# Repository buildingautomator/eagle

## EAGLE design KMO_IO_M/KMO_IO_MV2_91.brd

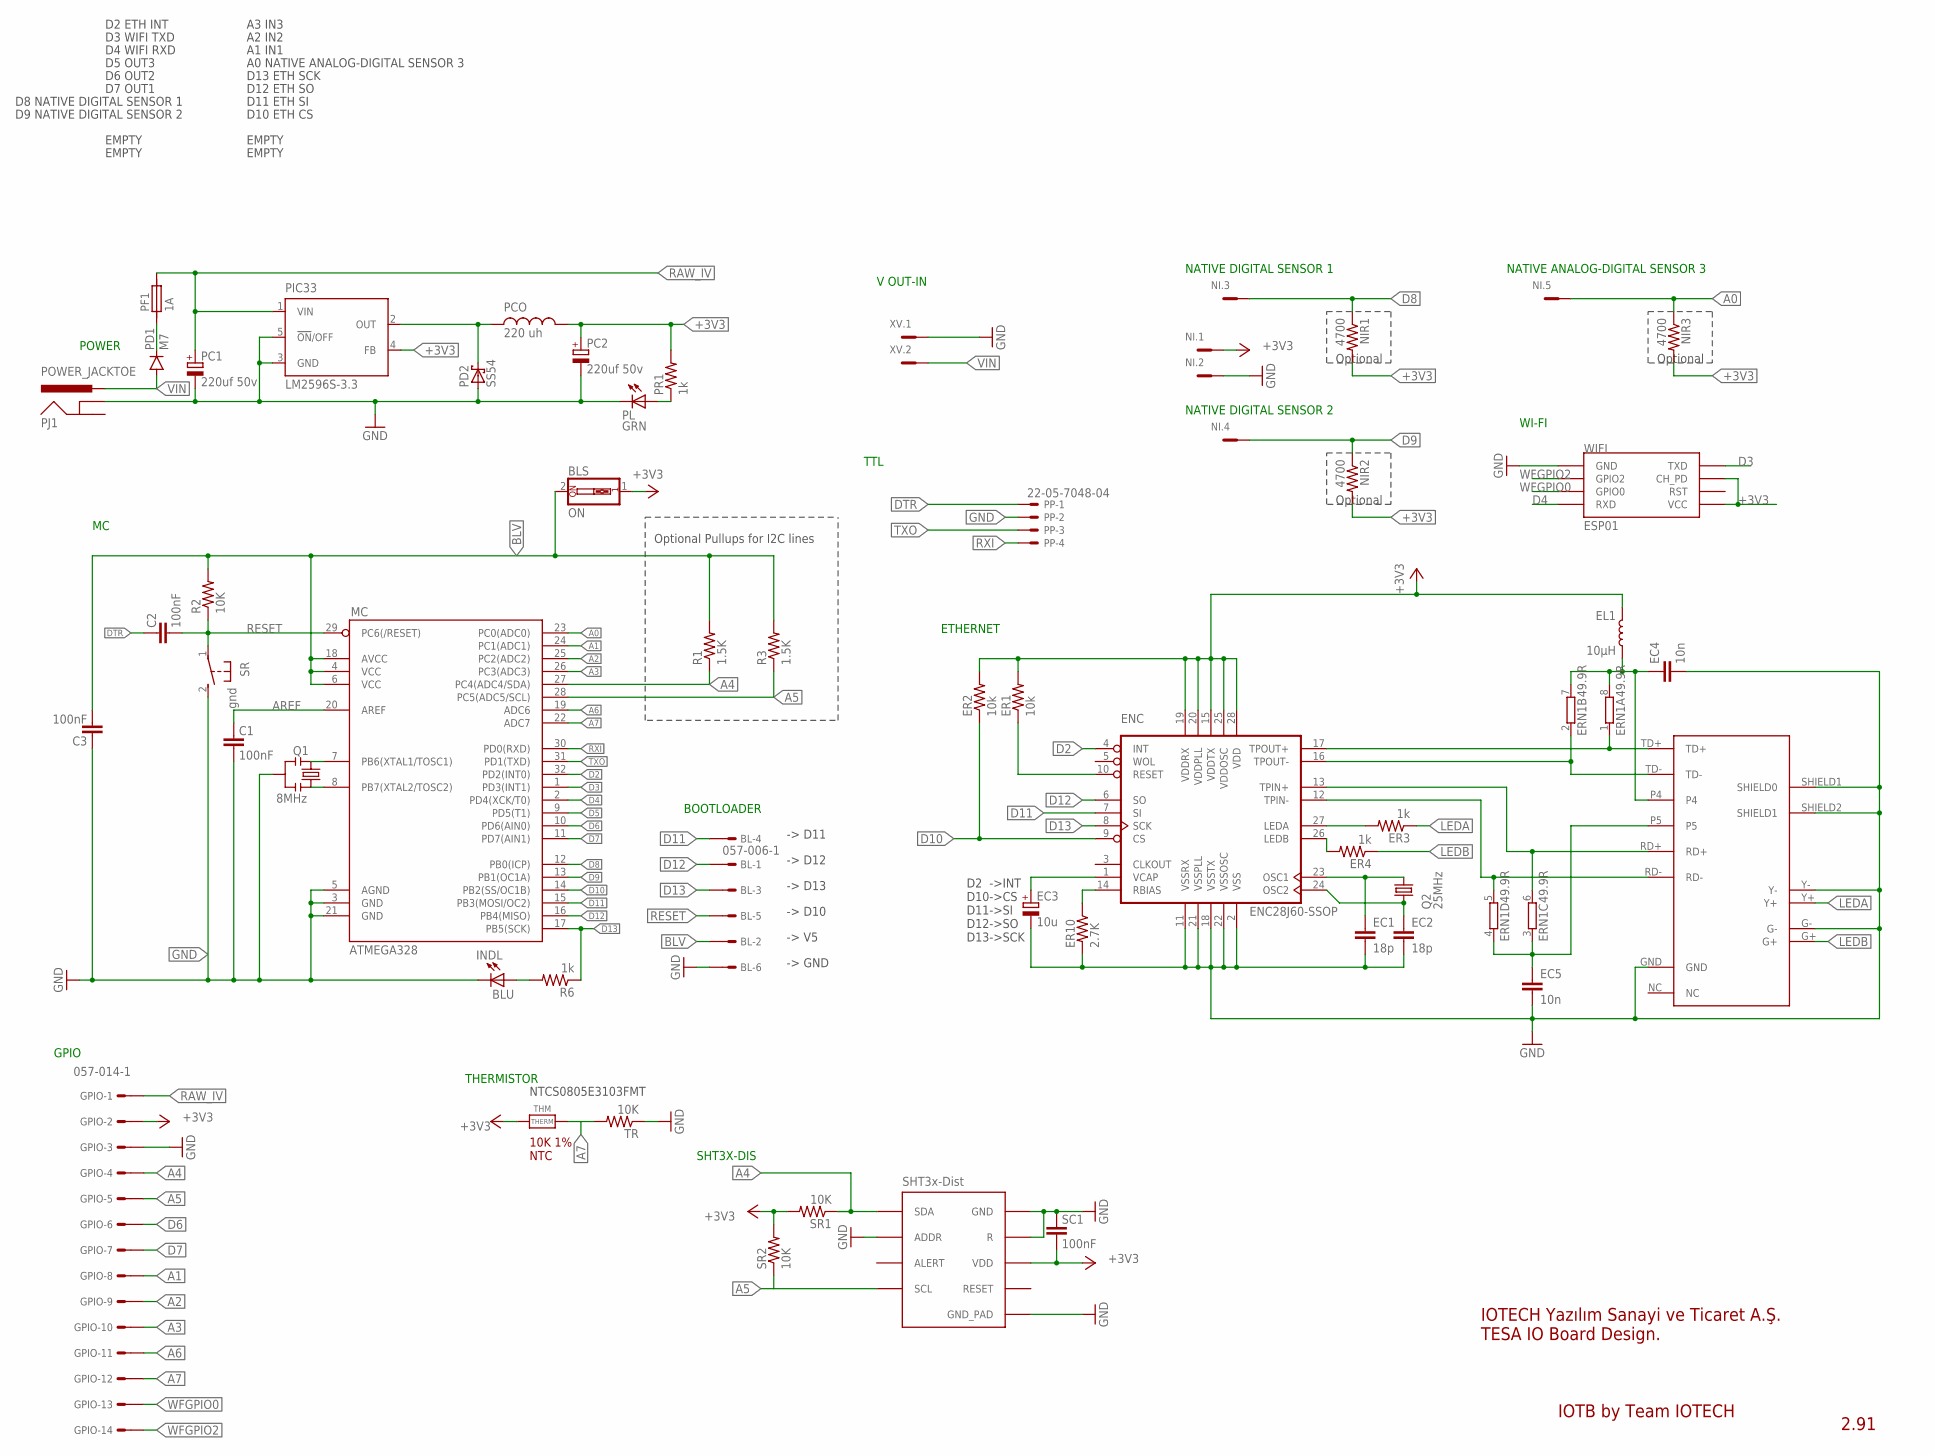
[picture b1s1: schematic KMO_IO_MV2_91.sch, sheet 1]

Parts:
BL: 057-006-1
BLS: ON; EDG-01
C1, C2, C3: 100nF; 0805
EC1, EC2: 18p; 0805
EC3: 10u; CT3216
EC4, EC5: 10n; 0805
EL1: 10µH; 0805
ENC: ENC28J60-SSOP; SSOP28
ER1, ER2: 10k; 0805
ER3, ER4: 1k; 0805
ER10: 2.7K; 0805
ERN1: 49.9R; 0603-ARV
GPIO: 057-014-1
INDL: BLU; CHIP-LED0805
MC: ATMEGA328; TQFP32-08
NI: MC5
NIR1, NIR2, NIR3: 4700; 0805
PC1, PC2: 220uf 50v; 140CLH-1010
PCO: 220 uh; MSS1260
PD1: M7; SMA-DIODE
PD2: SS54; SMB
PF1: 1A; 1820
PIC33: LM2596S-3.3; TO263-5
PJ1: POWER_JACKTOE; POWER_JACK_SMD_OVERPASTE_TOE
PL: GRN; CHIP-LED0805
PP: 22-05-7048-04; 7395-04
PR1: 1k; 0805
Q1: 8MHz; RESONATOR-SMD-1:1
Q2: 25MHz; 5.0X3.2_2
R1, R3: 1.5K; 0805
R2: 10K; 0805
R6: 1k; 0805
SC1: 100nF; 0805
SHT: SHT3X
SR: gnd; B3F-31XX
SR1, SR2: 10K; 0805
THM: THERM; MICROBUILDER_0805_NOTHERMALS
TR: 10K; 0805
U$2: HR911105A; RJ45
WIFI: ESP01
XV: MC2

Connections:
+3V3: BLS.1, EL1.1, ENC.15 (VDDTX), ENC.19 (VDDRX), ENC.20 (VDDPLL), ENC.25 (VDDOSC), ENC.28 (VDD), ER1.2, ER2.2, GPIO.2, NI.1, NIR1.2, NIR2.2, NIR3.2, PC2.+, PCO.P$1, PIC33.4 (FB), PR1.2, SC1.1, SHT.VDD, SR1.2, SR2.2, THM.1, WIFI.CH_PD, WIFI.VCC; also elsewhere on the board
A0: MC.23 (PC0(ADC0)), NI.5, NIR3.1
A1: GPIO.8, MC.24 (PC1(ADC1))
A2: GPIO.9, MC.25 (PC2(ADC2))
A3: GPIO.10, MC.26 (PC3(ADC3))
A4: GPIO.4, MC.27 (PC4(ADC4/SDA)), R1.1, SHT.SDA, SR1.1; also elsewhere on the board
A5: GPIO.5, MC.28 (PC5(ADC5/SCL)), R3.1, SHT.SCL, SR2.1; also elsewhere on the board
A6: GPIO.11, MC.19 (ADC6)
A7: GPIO.12, MC.22 (ADC7), THM.2, TR.2
AREF: C1.2, MC.20 (AREF)
BLV: BL.2, BLS.2, C3.1, MC.4 (VCC), MC.6 (VCC), MC.18 (AVCC), R1.2, R2.2, R3.2
D2: ENC.4 (INT), MC.32 (PD2(INT0))
D3: MC.1 (PD3(INT1)), WIFI.TX (TXD)
D4: MC.2 (PD4(XCK/T0)), WIFI.RX (RXD)
D5: MC.9 (PD5(T1)); also elsewhere on the board
D6: GPIO.6, MC.10 (PD6(AIN0))
D7: GPIO.7, MC.11 (PD7(AIN1))
D8: MC.12 (PB0(ICP)), NI.3, NIR1.1
D9: MC.13 (PB1(OC1A)), NI.4, NIR2.1
D10: ENC.9 (CS), ER2.1, MC.14 (PB2(SS/OC1B))
D11: BL.4, ENC.7 (SI), MC.15 (PB3(MOSI/OC2))
D12: BL.1, ENC.6 (SO), MC.16 (PB4(MISO))
D13: BL.3, ENC.8 (SCK), MC.17 (PB5(SCK)), R6.1
DTR: C2.2, PP.1
EP4: EC4.1, EL1.2, ERN1.7 (2), ERN1.8 (2), U$2.P4
EP5: EC5.1, ERN1.3 (1), ERN1.4 (1), U$2.P5
GND: BL.6, C1.1, C3.2, EC1.2, EC2.2, EC3.-, EC4.2, EC5.2, ENC.2 (VSS), ENC.11 (VSSRX), ENC.18 (VSSTX), ENC.21 (VSSPLL), ENC.22 (VSSOSC), ER10.2, GPIO.3, INDL.C, MC.3 (GND), MC.5 (AGND), MC.21 (GND), NI.2, PC1.-, PC2.-, PD2.A, PIC33.3 (GND), PIC33.5 (!ON!/OFF), PJ1.GND (GNDBREAK), PL.C, PP.2, Q1.2, SC1.2, SHT.ADDR, SHT.GND, SHT.GND_PAD, SHT.R, SR.2 (S), TR.1, U$2.G-, U$2.GND, U$2.SHIELD1 (SHIELD0), U$2.SHIELD2 (SHIELD1), U$2.Y-, WIFI.GND, XV.1; also elsewhere on the board
LEDA: ER3.1, U$2.Y+
LEDB: ER4.1, U$2.G+
unnamed: PD1.C, PF1.1
unnamed: INDL.A, R6.2
unnamed: ENC.27 (LEDA), ER3.2
unnamed: MC.8 (PB7(XTAL2/TOSC2)), Q1.3
unnamed: PL.A, PR1.1
unnamed: EC3.+, ENC.1 (VCAP)
unnamed: ENC.26 (LEDB), ER4.2
unnamed: MC.7 (PB6(XTAL1/TOSC1)), Q1.1
unnamed: PCO.P$2, PD2.C, PIC33.2 (OUT)
unnamed: ENC.10 (RESET), ER1.1
unnamed: ENC.14 (RBIAS), ER10.1
unnamed: EC2.1, ENC.24 (OSC2), Q2.1
unnamed: EC1.1, ENC.23 (OSC1), Q2.2
RAW_IV: GPIO.1, PC1.+, PF1.2, PIC33.1 (VIN)
RD+: ENC.13 (TPIN+), ERN1.6 (2), U$2.RD+
RD-: ENC.12 (TPIN-), ERN1.5 (2), U$2.RD-
RESET: BL.5, C2.1, MC.29 (PC6(/RESET)), R2.1, SR.1
RXI: MC.30 (PD0(RXD)), PP.4
TD+: ENC.17 (TPOUT+), ERN1.1, U$2.TD+
TD-: ENC.16 (TPOUT-), ERN1.2 (1), U$2.TD-
TXO: MC.31 (PD1(TXD)), PP.3
VIN: PD1.A, PJ1.VIN0 (PWR), XV.2
WFGPIO0: GPIO.13, WIFI.GPIO0
WFGPIO2: GPIO.14, WIFI.GPIO2

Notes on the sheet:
POWER
NATIVE DIGITAL SENSOR 1
NATIVE DIGITAL SENSOR 2
WI-FI
NATIVE ANALOG-DIGITAL SENSOR 3
IOTB by Team IOTECH
2.91
ETHERNET
D2 ->INT D10->CS D11->SI D12->SO D13->SCK
TTL
IOTECH Yazılım Sanayi ve Ticaret A.Ş. TESA IO Board Design.
Optional Pullups for I2C lines
D2 ETH INT
D8 NATIVE DIGITAL SENSOR 1
D9 NATIVE DIGITAL SENSOR 2
EMPTY
A3 IN3
A2 IN2
A1 IN1
A0 NATIVE ANALOG-DIGITAL SENSOR 3
D13 ETH SCK
D12 ETH SO
D11 ETH SI
D10 ETH CS
D4 WIFI RXD
D3 WIFI TXD
D7 OUT1
D6 OUT2
D5 OUT3
BOOTLOADER
-> D11
-> D12
-> D13
-> D10
-> V5
-> GND
Optional
V OUT-IN
GPIO
NTCS0805E3103FMT

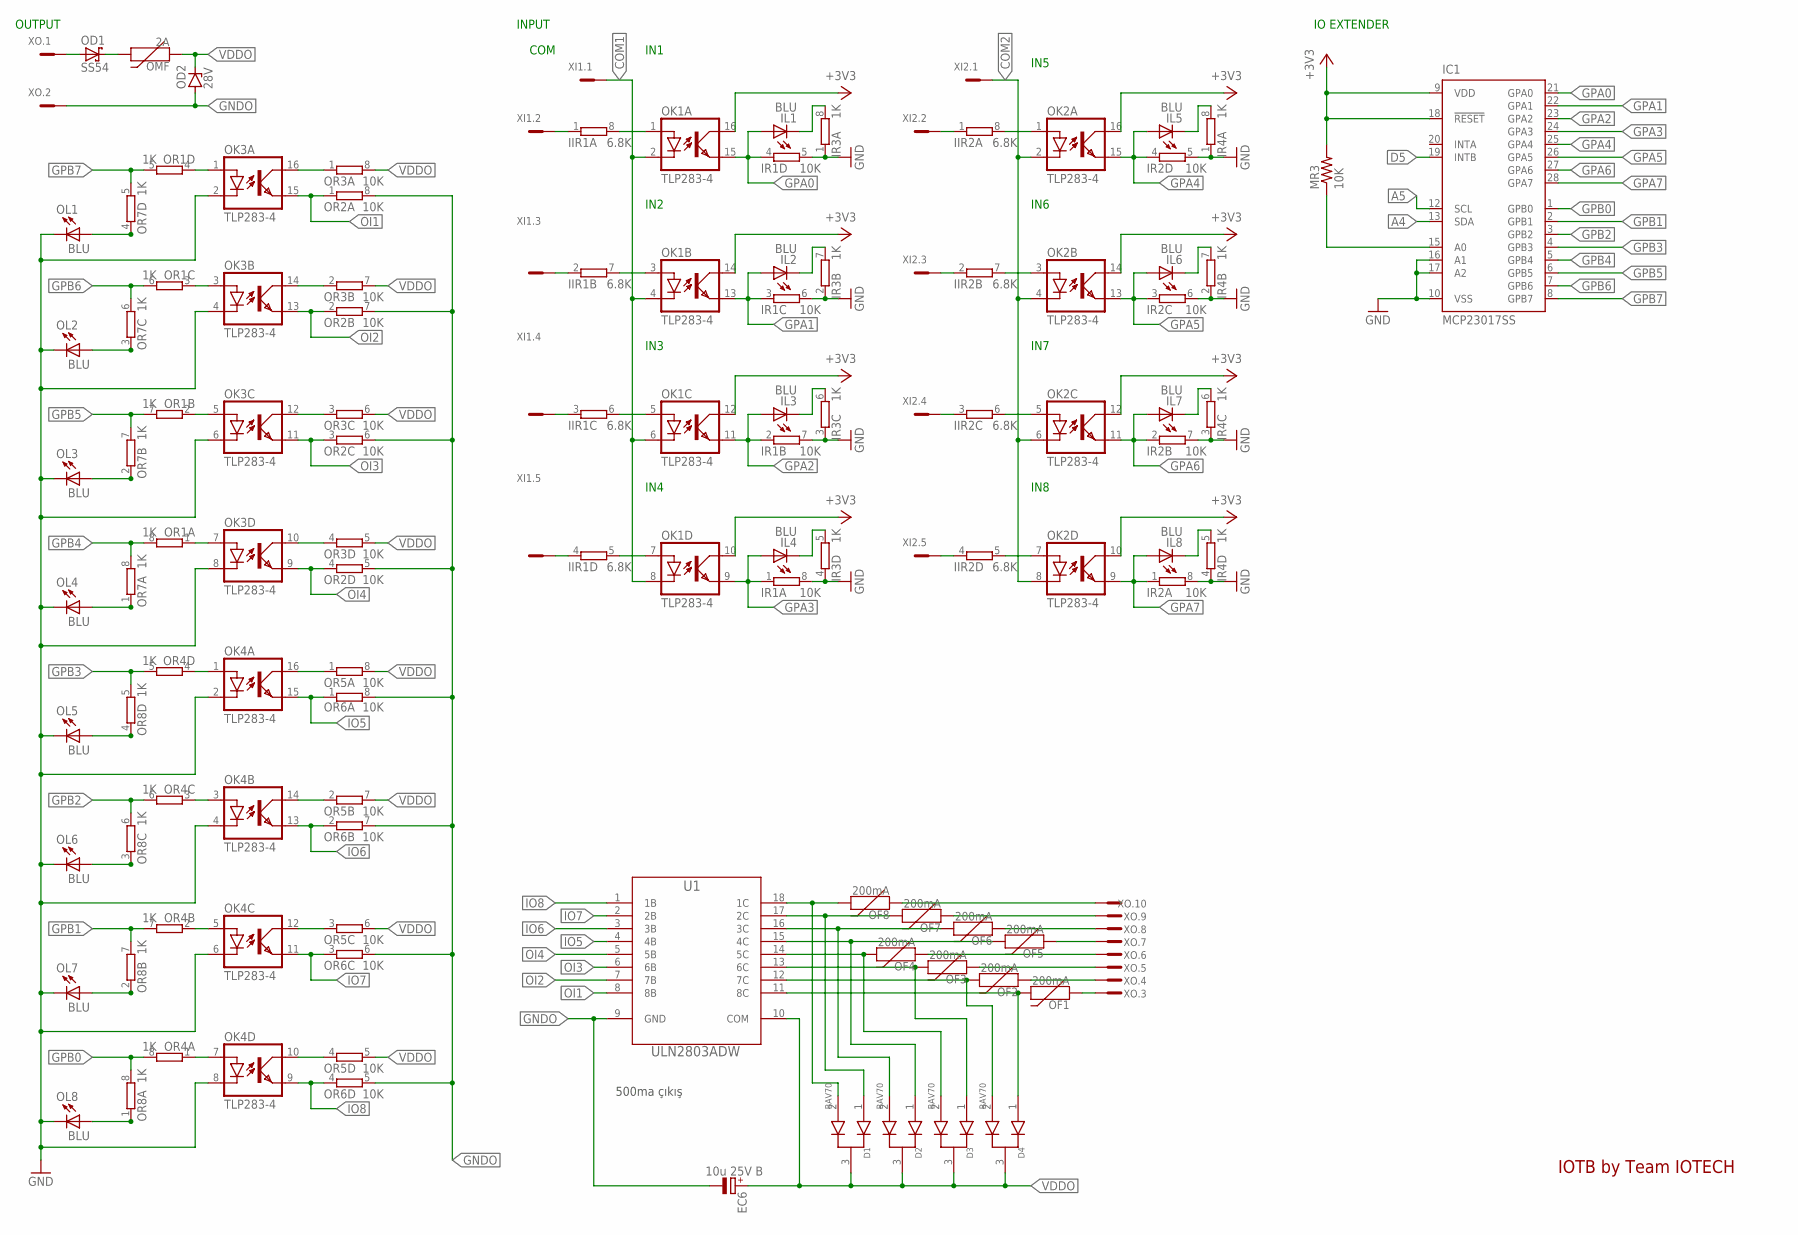
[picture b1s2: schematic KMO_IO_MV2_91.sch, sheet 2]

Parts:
D1, D2, D3, D4: BAV70; SOT-23-3
EC6: 10u 25V B; SMC_B
IC1: MCP23017SS; SSOP28
IIR1, IIR2: 6.8K; 0603-ARV
IL1, IL2, IL3, IL4, IL5, IL6, IL7, IL8: BLU; CHIP-LED0805
IR1, IR2: 10K; 0603-ARV
IR3, IR4: 1K; 0603-ARV
MR3: 10K; 0805
OD1: SS54; SMB
OD2: 28V; SMB
OF1, OF2, OF3, OF4, OF5, OF6, OF7, OF8: 200mA; 1206
OK1, OK2, OK3, OK4: TLP283-4; MINI-FLAT-16
OL1, OL2, OL3, OL4, OL5, OL6, OL7, OL8: BLU; CHIP-LED0805
OMF: 2A; 1206
OR1, OR4, OR7, OR8: 1K; 0603-ARV
OR2, OR3, OR5, OR6: 10K; 0603-ARV
U1: ULN2803ADW; SOIC127P1030X265-18N
XI1, XI2: MC5
XO: MC10

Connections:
+3V3: IC1.9 (VDD), IC1.18 (!RESET), MR3.2, OK1.10 (COL), OK1.12 (COL), OK1.14 (COL), OK1.16 (COL), OK2.10 (COL), OK2.12 (COL), OK2.14 (COL), OK2.16 (COL); also elsewhere on the board
A4: IC1.13 (SDA); also elsewhere on the board
A5: IC1.12 (SCL); also elsewhere on the board
COM1: OK1.2 (C), OK1.4 (C), OK1.6 (C), OK1.8 (C), XI1.1
COM2: OK2.2 (C), OK2.4 (C), OK2.6 (C), OK2.8 (C), XI2.1
D5: IC1.19 (INTB); also elsewhere on the board
GND: IC1.10 (VSS), IC1.16 (A1), IC1.17 (A2), IR1.5 (2), IR1.6 (2), IR1.7 (2), IR1.8 (2), IR2.5 (2), IR2.6 (2), IR2.7 (2), IR2.8 (2), IR3.1, IR3.2 (1), IR3.3 (1), IR3.4 (1), IR4.1, IR4.2 (1), IR4.3 (1), IR4.4 (1), OK3.2 (C), OK3.4 (C), OK3.6 (C), OK3.8 (C), OK4.2 (C), OK4.4 (C), OK4.6 (C), OK4.8 (C), OL1.C, OL2.C, OL3.C, OL4.C, OL5.C, OL6.C, OL7.C, OL8.C; also elsewhere on the board
GNDO: EC6.-, OD2.A, OR2.5 (2), OR2.6 (2), OR2.7 (2), OR2.8 (2), OR6.5 (2), OR6.6 (2), OR6.7 (2), OR6.8 (2), U1.9 (GND), XO.2
GPA0: IC1.21 (GPA0), IL1.A, IR1.4 (1), OK1.15 (EMIT)
GPA1: IC1.22 (GPA1), IL2.A, IR1.3 (1), OK1.13 (EMIT)
GPA2: IC1.23 (GPA2), IL3.A, IR1.2 (1), OK1.11 (EMIT)
GPA3: IC1.24 (GPA3), IL4.A, IR1.1, OK1.9 (EMIT)
GPA4: IC1.25 (GPA4), IL5.A, IR2.4 (1), OK2.15 (EMIT)
GPA5: IC1.26 (GPA5), IL6.A, IR2.3 (1), OK2.13 (EMIT)
GPA6: IC1.27 (GPA6), IL7.A, IR2.2 (1), OK2.11 (EMIT)
GPA7: IC1.28 (GPA7), IL8.A, IR2.1, OK2.9 (EMIT)
GPB0: IC1.1 (GPB0), OR4.8 (2), OR8.8 (2)
GPB1: IC1.2 (GPB1), OR4.7 (2), OR8.7 (2)
GPB2: IC1.3 (GPB2), OR4.6 (2), OR8.6 (2)
GPB3: IC1.4 (GPB3), OR4.5 (2), OR8.5 (2)
GPB4: IC1.5 (GPB4), OR1.8 (2), OR7.8 (2)
GPB5: IC1.6 (GPB5), OR1.7 (2), OR7.7 (2)
GPB6: IC1.7 (GPB6), OR1.6 (2), OR7.6 (2)
GPB7: IC1.8 (GPB7), OR1.5 (2), OR7.5 (2)
IO5: OK4.15 (EMIT), OR6.1, U1.4 (4B)
IO6: OK4.13 (EMIT), OR6.2 (1), U1.3 (3B)
IO7: OK4.11 (EMIT), OR6.3 (1), U1.2 (2B)
IO8: OK4.9 (EMIT), OR6.4 (1), U1.1 (1B)
unnamed: OD1.A, XO.1
unnamed: IC1.15 (A0), MR3.1
unnamed: OD1.C, OMF.2
unnamed: OF8.1, XO.10
unnamed: D1.1, OF7.2, U1.17 (2C)
unnamed: OK3.1 (A), OR1.4 (1)
unnamed: IL1.C, IR3.8 (2)
unnamed: IIR1.1, XI1.2
unnamed: IL2.C, IR3.7 (2)
unnamed: IL3.C, IR3.6 (2)
unnamed: IL4.C, IR3.5 (2)
unnamed: IL5.C, IR4.8 (2)
unnamed: IL6.C, IR4.7 (2)
unnamed: IL7.C, IR4.6 (2)
unnamed: IIR1.2 (1), XI1.3
unnamed: IIR1.8 (2), OK1.1 (A)
unnamed: IIR1.7 (2), OK1.3 (A)
unnamed: IIR1.6 (2), OK1.5 (A)
unnamed: IIR1.5 (2), OK1.7 (A)
unnamed: IIR1.3 (1), XI1.4
unnamed: IIR1.4 (1), XI1.5
unnamed: OK3.3 (A), OR1.3 (1)
unnamed: IIR2.1, XI2.2
unnamed: IIR2.8 (2), OK2.1 (A)
unnamed: IIR2.2 (1), XI2.3
unnamed: IIR2.7 (2), OK2.3 (A)
unnamed: IIR2.3 (1), XI2.4
unnamed: IIR2.6 (2), OK2.5 (A)
unnamed: IIR2.4 (1), XI2.5
unnamed: IIR2.5 (2), OK2.7 (A)
unnamed: IL8.C, IR4.5 (2)
unnamed: OK3.5 (A), OR1.2 (1)
unnamed: OK3.7 (A), OR1.1
unnamed: D1.2, OF8.2, U1.18 (1C)
unnamed: OK3.16 (COL), OR3.1
unnamed: D2.2, OF6.2, U1.16 (3C)
unnamed: D2.1, OF5.2, U1.15 (4C)
unnamed: OF7.1, XO.9
unnamed: OF6.1, XO.8
unnamed: OK3.14 (COL), OR3.2 (1)
unnamed: OF5.1, XO.7
unnamed: OF4.1, XO.6
unnamed: OK3.12 (COL), OR3.3 (1)
unnamed: D3.1, OF3.2, U1.13 (6C)
unnamed: OK3.10 (COL), OR3.4 (1)
unnamed: D4.2, OF2.2, U1.12 (7C)
unnamed: OL1.A, OR7.4 (1)
unnamed: OL2.A, OR7.3 (1)
unnamed: OL3.A, OR7.2 (1)
unnamed: OL4.A, OR7.1
unnamed: D4.1, OF1.2, U1.11 (8C)
unnamed: D3.2, OF4.2, U1.14 (5C)
unnamed: OF3.1, XO.5
unnamed: OF2.1, XO.4
unnamed: OF1.1, XO.3
unnamed: OK4.1 (A), OR4.4 (1)
unnamed: OK4.3 (A), OR4.3 (1)
unnamed: OK4.5 (A), OR4.2 (1)
unnamed: OK4.7 (A), OR4.1
unnamed: OK4.16 (COL), OR5.1
unnamed: OK4.14 (COL), OR5.2 (1)
unnamed: OK4.12 (COL), OR5.3 (1)
unnamed: OK4.10 (COL), OR5.4 (1)
unnamed: OL5.A, OR8.4 (1)
unnamed: OL6.A, OR8.3 (1)
unnamed: OL7.A, OR8.2 (1)
unnamed: OL8.A, OR8.1
OI1: OK3.15 (EMIT), OR2.1, U1.8 (8B)
OI2: OK3.13 (EMIT), OR2.2 (1), U1.7 (7B)
OI3: OK3.11 (EMIT), OR2.3 (1), U1.6 (6B)
OI4: OK3.9 (EMIT), OR2.4 (1), U1.5 (5B)
VDDO: D1.3, D2.3, D3.3, D4.3, EC6.+, OD2.C, OMF.1, OR3.5 (2), OR3.6 (2), OR3.7 (2), OR3.8 (2), OR5.5 (2), OR5.6 (2), OR5.7 (2), OR5.8 (2), U1.10 (COM)

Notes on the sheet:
IOTB by Team IOTECH
INPUT
IN1
IN2
IN3
IN4
IN5
IN6
IN7
IN8
COM
OUTPUT
IO EXTENDER
500ma çıkış

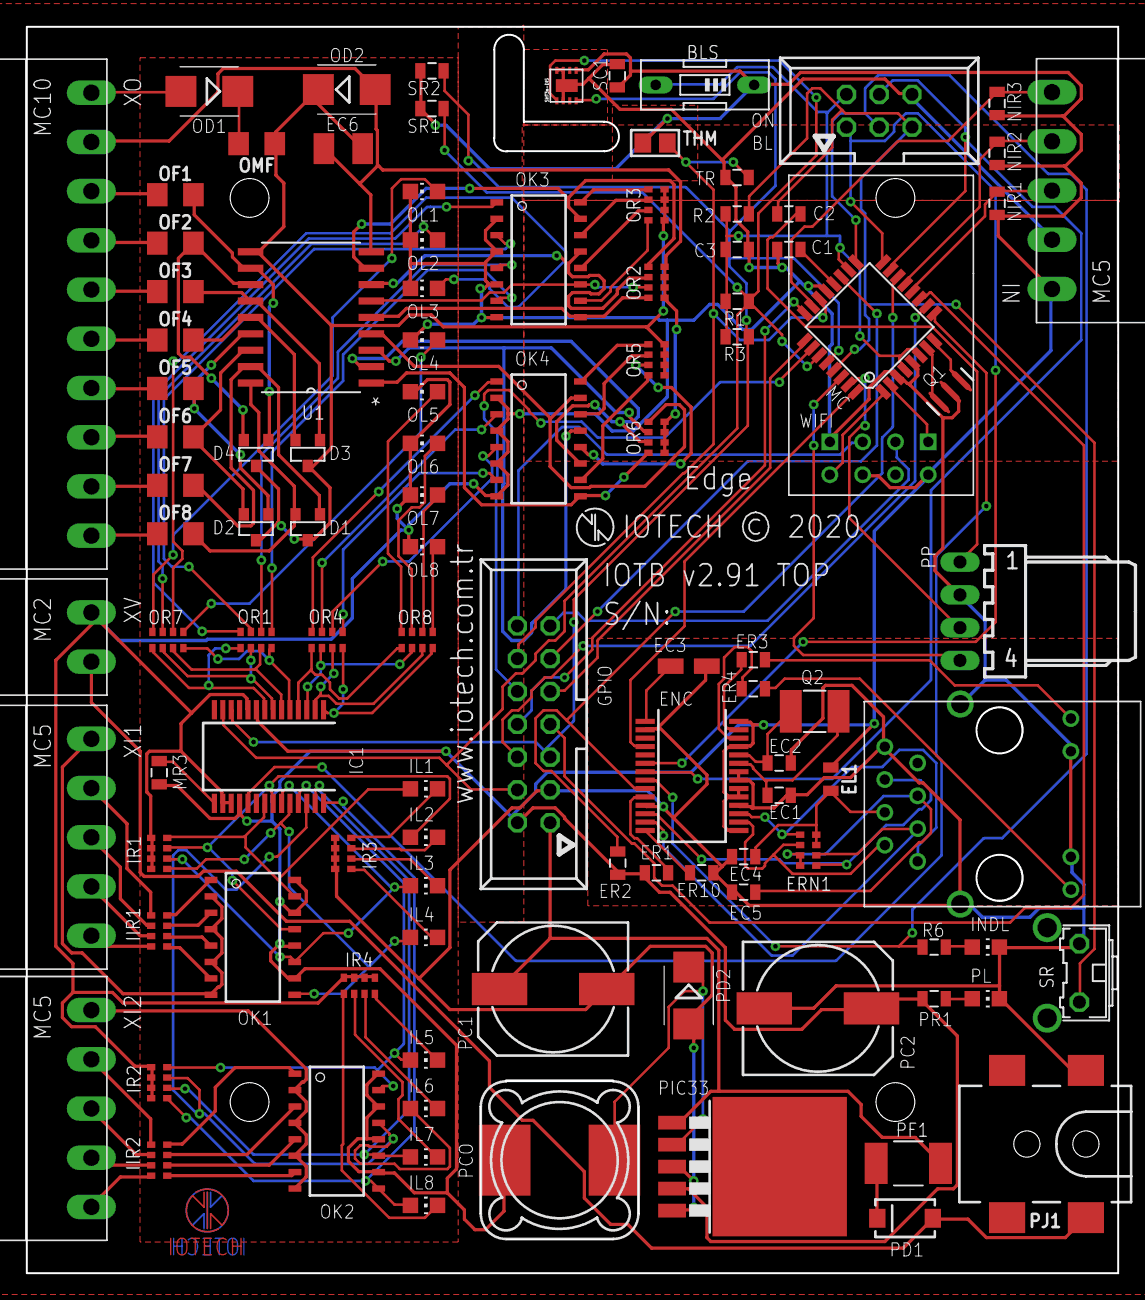
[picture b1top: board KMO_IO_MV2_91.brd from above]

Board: 2 copper layers, 84.5 x 96.5 mm, 110 parts (1 on the bottom side), 148 nets.

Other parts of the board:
U$1, U$4: IOTECH_COPPER_W_TEXT

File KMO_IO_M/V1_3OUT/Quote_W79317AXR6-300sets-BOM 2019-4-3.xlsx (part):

300sets | total | remark | Answ | Quantity | Part | Value | Device | Package | Description MF MPN OC_FARNELL OC_NEWARK PROD_ID SF_ID SPICEPREFIX VALUE
 | 0 | pls offer correct part number | FC68148S, PRT-12748 Barrel Connector | 1 | BL | 057-006-1 | 057-006-1 | 057-006-1 | CONNECTOR unknown unknown
 | 0 | pls offer part number | DS01V, BD01 | 1 | BLS |  | SW_DIP-1 | EDG-01 | DIP SWITCH
3.3000000000000002E-2 | 9.9 |  |  | 1 | C1 | 100nF | CAP0805 | 805 | Capacitor
3.3000000000000002E-2 | 9.9 |  |  | 1 | C2 | 100nF | CAP0805 | 805 | Capacitor
3.3000000000000002E-2 | 9.9 |  |  | 1 | C3 | 100nF | CAP0805 | 805 | Capacitor
8.8000000000000005E-3 | 2.64 |  |  | 1 | EC1 | 18p | CAP0805 | 805 | Capacitor
8.8000000000000005E-3 | 2.64 |  |  | 1 | EC2 | 18p | CAP0805 | 805 | Capacitor
0.13200000000000001 | 39.6 | we offer TANT 10UF 16V A3216,OK? | TANT 10UF 16V A3216 | 1 | EC3 | 10u | CPOL-EUCT3216 | CT3216 | POLARIZED CAPACITOR, European symbol C
8.8000000000000005E-3 | 2.64 |  |  | 1 | EC4 | 10n | CAP0805 | 805 | Capacitor
8.8000000000000005E-3 | 2.64 |  |  | 1 | EC5 | 10n | CAP0805 | 805 | Capacitor
 | 0 | pls offer part number |  | 1 | EL1 | 10礖 | INDUCTOR-0805-3.3UH | 805 | Inductors NDUC-13076 3.3礖/?0%/450mA
2.31 | 693 | we offer ENC28J60/SS SSOP28,OK? | ENC28J60/SS SSOP28 | 1 | ENC | ENC28J60-SSOP | ENC28J60-SSOP | SSOP28 | Microchip 10Mbit Eth. contoller with SPI interface
8.8000000000000005E-3 | 2.64 |  |  | 1 | ER1 | 10k | RESISTOR0805-RES | 805 | Resistor
8.8000000000000005E-3 | 2.64 |  |  | 1 | ER2 | 10k | RESISTOR0805-RES | 805 | Resistor
8.8000000000000005E-3 | 2.64 |  |  | 1 | ER3 | 1k | RESISTOR0805-RES | 805 | Resistor
8.8000000000000005E-3 | 2.64 |  |  | 1 | ER4 | 1k | RESISTOR0805-RES | 805 | Resistor
8.8000000000000005E-3 | 2.64 | do not have 50R ,we offer 49.9R,OK? | 49.9R | 1 | ER6 | 50R | RESISTOR0805-RES | 805 | Resistor
8.8000000000000005E-3 | 2.64 | do not have 50R ,we offer 49.9R,OK? | 49.9R | 1 | ER7 | 50R | RESISTOR0805-RES | 805 | Resistor
8.8000000000000005E-3 | 2.64 | do not have 50R ,we offer 49.9R,OK? | 49.9R | 1 | ER8 | 50R | RESISTOR0805-RES | 805 | Resistor
8.8000000000000005E-3 | 2.64 | do not have 50R ,we offer 49.9R,OK? | 49.9R | 1 | ER9 | 50R | RESISTOR0805-RES | 805 | Resistor
8.8000000000000005E-3 | 2.64 | we offer LTST-C170TBKT blue,OK? | LTST-C170TBKT blue | 1 | ER10 | 2.7K | RESISTOR0805-RES | 805 | Resistor
3.85E-2 | 11.55 | we offer LTST-C170TBKT blue,OK? | LTST-C170TBKT blue | 1 | IL1 | BLU | LEDCHIP-LED0805 | CHIP-LED0805 | LED
3.85E-2 | 11.55 | we offer LTST-C170TBKT blue,OK? | LTST-C170TBKT blue | 1 | IL2 | BLU | LEDCHIP-LED0805 | CHIP-LED0805 | LED
3.85E-2 | 11.55 | we offer LTST-C170TBKT,blue,OK? | LTST-C170TBKT blue | 1 | IL3 | BLU | LEDCHIP-LED0805 | CHIP-LED0805 | LED
3.85E-2 | 11.55 | we offer LTST-C170TBKT,blue,OK? | LTST-C170TBKT blue | 1 | IL4 | BLU | LEDCHIP-LED0805 | CHIP-LED0805 | LED
3.85E-2 | 11.55 | we offer LTST-C170TBKT blue,OK? | LTST-C170TBKT blue | 1 | IL5 | BLU | LEDCHIP-LED0805 | CHIP-LED0805 | LED
3.85E-2 | 11.55 | we offer LTST-C170TBKT blue,OK? | LTST-C170TBKT blue | 1 | IL6 | BLU | LEDCHIP-LED0805 | CHIP-LED0805 | LED
3.85E-2 | 11.55 | we offer LTST-C170TBKT blue,OK? | LTST-C170TBKT blue | 1 | IL7 | BLU | LEDCHIP-LED0805 | CHIP-LED0805 | LED
3.85E-2 | 11.55 | we offer LTST-C170TBKT blue,OK? | LTST-C170TBKT blue | 1 | INDL | BLU | LEDCHIP-LED0805 | CHIP-LED0805 | LED
8.8000000000000005E-3 | 2.64 |  |  | 1 | IR | 10K | RESISTOR0805-RES | 805 | Resistor
8.8000000000000005E-3 | 2.64 |  |  | 1 | IR1 | 1K | RESISTOR0805-RES | 805 | Resistor
8.8000000000000005E-3 | 2.64 |  |  | 1 | IR2 | 1K | RESISTOR0805-RES | 805 | Resistor
8.8000000000000005E-3 | 2.64 |  |  | 1 | IR3 | 1K | RESISTOR0805-RES | 805 | Resistor
8.8000000000000005E-3 | 2.64 |  |  | 1 | IR4 | 1K | RESISTOR0805-RES | 805 | Resistor
8.8000000000000005E-3 | 2.64 |  |  | 1 | IR5 | 1K | RESISTOR0805-RES | 805 | Resistor
8.8000000000000005E-3 | 2.64 |  |  | 1 | IR6 | 1K | RESISTOR0805-RES | 805 | Resistor
8.8000000000000005E-3 | 2.64 |  |  | 1 | IR7 | 1K | RESISTOR0805-RES | 805 | Resistor
 | 0
 | 0
 | 0
3.85E-2 | 11.55 | 1N4007 SMA |  | 1 | OD1 | M7 | DIODESMA | SMA-DIODE | Diode
3.85E-2 | 11.55 | 1N4007 SMA |  | 1 | OD2 | M7 | DIODESMA | SMA-DIODE | Diode
3.85E-2 | 11.55 | 1N4007 SMA |  | 1 | OD3 | M7 | DIODESMA | SMA-DIODE | Diode
3.85E-2 | 11.55 | we offer LTST-C170KSKT yellow,OK? | LTST-C170KSKT yellow | 1 | OL1 | YLW | LEDCHIP-LED0805 | CHIP-LED0805 | LED
3.85E-2 | 11.55 | we offer LTST-C170KSKT yellow,OK? | LTST-C170KSKT yellow | 1 | OL2 | YLW | LEDCHIP-LED0805 | CHIP-LED0805 | LED
3.85E-2 | 11.55 | we offer LTST-C170KSKT yellow,OK? | LTST-C170KSKT yellow | 1 | OL3 | YLW | LEDCHIP-LED0805 | CHIP-LED0805 | LED
 | 0 | out of stock,pls advise replacement? |  | 1 | OQ1 | IRF3707S | IRF3704S | D2PACK | SMPS MOSFET
 | 0 | out of stock,pls advise replacement? |  | 1 | OQ2 | IRF3707S | IRF3704S | D2PACK | SMPS MOSFET
 | 0 | out of stock,pls advise replacement? |  | 1 | OQ3 | IRF3707S | IRF3704S | D2PACK | SMPS MOSFET
8.8000000000000005E-3 | 2.64 |  |  | 1 | OR1 | 1K | RESISTOR0805-RES | 805 | Resistor
8.8000000000000005E-3 | 2.64 |  |  | 1 | OR2 | 1K | RESISTOR0805-RES | 805 | Resistor
8.8000000000000005E-3 | 2.64 |  |  | 1 | OR3 | 1K | RESISTOR0805-RES | 805 | Resistor
 | 0 | pls offer part number |  | 1 | PC1 | 470uf 25v | CPOL-EU140CLH-1010 | 140CLH-1010 | POLARIZED CAPACITOR, European symbol C
 | 0 | pls offer part number |  | 1 | PC2 | 220uf 50v | CPOL-EU140CLH-1010 | 140CLH-1010 | POLARIZED CAPACITOR, European symbol C
1.4850000000000001 | 445.50000000000006 | MSS1260-224KLD |  | 1 | PCO | 220 uh | MSS1260 | MSS1260 | SMT Power Inductor
5.5E-2 | 16.5 | 1N4007 |  | 1 | PD1 | M7 | DIODESMA | SMA-DIODE | Diode
0.11 | 33 |  |  | 1 | PD2 | SS54 | SCHOTTKY-DIODESMD | SMB | Schottky Diode
 | 0 | pls offer correct part number |  | 1 | PF1 | 1A | SIBA194600 | 1820 | SIBA PTC-Fuses, Series 194600, 1812 (4.5 3.2)mm
1.76 | 528 | LM2596S-ADJ/NOPB |  | 1 | PIC33 | LM2596S | LM2596S | TO263-5 | SIMPLE SWITCHER?Power Converter 150 kHz 3A Step-Down Voltage Regulator NATIONAL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
 | 0 | pls offer part number |  | 1 | PJ1 | POWER_JACKTOE | POWER_JACKTOE | POWER_JACK_SMD_OVERPASTE_TOE | Power Jack Connector CONN-08106 PRT-12748
3.85E-2 | 11.55 | we offer LTST-C170KGKT green,OK? |  | 1 | PL | GRN | LEDCHIP-LED0805 | CHIP-LED0805 | LED
 | 0 | pls offer correct part number |  | 1 | PP | 22-05-7048-04 | 22-05-7048-04 | 2007100 | CONNECTOR MOLEX unknown unknown 90 Degree horizontal
8.8000000000000005E-3 | 2.64 |  |  | 1 | PR1 | 1k | RESISTOR0805-RES | 805 | Resistor
 | 0 | pls offer part number |  | 1 | Q1 | 8MHz | RESONATOR1:1 | RESONATOR-SMD-1:1 | Resonator
 | 0 | pls offer part number |  | 1 | Q2 | 25MHz | KX-9B | 5.0X3.2_2 | Quartz Crystals (MHz) SMD:
 | 0
8.8000000000000005E-3 | 2.64 |  |  | 1 | R2 | 10K | RESISTOR0805-RES | 805 | Resistor
 | 0
8.8000000000000005E-3 | 2.64 |  |  | 1 | R6 | 1k | RESISTOR0805-RES | 805 | Resistor
0.27500000000000002 | 82.5 | we offer B3F-3100,pls confirm? |  | 1 | SR |  | 31-XX | B3F-31XX | OMRON SWITCH B3F-3100 959704 36M3582
 | 0 | pls offer part number |  | 1 | SV1 |  | S03P | S03P | AMP MT CONNECTOR 90 Degree horizontal
 | 0 | pls offer part number |  | 1 | SV2 |  | S03P | S03P | AMP MT CONNECTOR 90 Degree horizontal
 | 0 | pls offer part number |  | 1 | SV3 |  | S03P | S03P | AMP MT CONNECTOR 90 Degree horizontal
1.3420000000000001 | 402.6 |  |  | 1 | U$2 | HR911105A | HR911105A | RJ45
1.4850000000000001 | 445.50000000000006 | we offer ATMEGA328P-AU ,pls confirm? |  | 1 | U1 | ATMEGA328 | ATMEGA168 | TQFP32-08
 | 0 |  |  | 1
3.85E-2 | 11.55 | we offer LTST-C170TBKT blue? |  | 1 | WIL0 | BLU | LEDCHIP-LED0805 | CHIP-LED0805 | LED
3.85E-2 | 11.55 | we offer LTST-C170TBKT blue,OK? |  | 1 | WIL2 | BLU | LEDCHIP-LED0805 | CHIP-LED0805 | LED
8.8000000000000005E-3 | 2.64 |  |  | 1 | WIR0 | 1K | RESISTOR0805-RES | 805 | Resistor
8.8000000000000005E-3 | 2.64 |  |  | 1 | WIR2 | 1K | RESISTOR0805-RES | 805 | Resistor
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
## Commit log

2014-05-15 Start
    Start Point
2014-05-15 atmega module
    atmega module
2014-05-15 switch m1
2014-05-16 TACK
2014-05-16 Text
2014-05-20 modify
2014-05-26 armed base
2014-06-19 smd2
2014-06-19 modbus
2014-06-20 last
2014-06-20 7805
2014-06-24 modbus in-out
2014-06-25 rtu org
2014-06-26 MCU almost
2014-06-26 net class settings
2014-06-26 Eagle Settings Pic
2014-06-27 mcu for test
2014-06-27 cnc test circuit
2014-06-28 CNC conf 1
2014-06-30 clean
2014-07-01 fuse replace
2014-07-01 IO rev
2014-07-02 rtu fuse
2014-07-03 DCU
    DCU seperation and CNC settings update for another shot.
2014-07-03 modbus board meanless update
2014-07-09 saksi
2014-07-10 Sula Matik
2014-07-10 done
2014-07-13 pcb gcode rev
2014-07-15 sula
2014-07-15 trimpod
2014-08-26 sula v1
2014-08-27 sula5110
2014-08-27 sula1
2014-09-06 v1 home ready
2015-01-11 RIO_V0
2015-01-24 sulav2
2015-01-29 battry buzzer eksik
2015-01-29 tamam
2015-02-01 almost v2
2015-02-01 sync
2016-01-08 begin mariomat
2017-03-05 pro mini
2017-03-05 1 layer karasol
2017-03-05 pcb gcode karasol
2017-03-05 gcode calıs karasol
2017-03-07 pcb router ayarlar
2017-03-11 cnc weezy geçiş
2017-03-12 karasol son
2017-03-12 karasol rev
2017-03-24 power
2017-03-24 ardu bef
2017-03-24 clk lib ard
2017-03-24 mosfet bef
2017-03-24 bef check
2017-03-27 gcode
2017-04-09 karabox cnc proto1
2017-04-18 value changec
2017-04-19 ptototip 2 için son ayarlar
    bağlantı yerleri ve mosfet çıkış diyod yeri düzenlendi. izole
    kalınlştırıldı.
2017-04-21 pto2 v0.1
2017-04-21 proto 2 v 0.2 ready
2017-04-23 logo lib
2017-04-23 proto 2 in action
2018-08-27 KMO Base
2018-08-27 rj45
2018-08-28 input haric
2018-08-28 isimlendirme std
2018-08-29 lib modified
2018-08-29 yerlestir
2018-08-31 input eksik
2018-08-31 route ve lable eksik
2018-08-31 prototip
2018-08-31 gerber
2018-09-04 modif
2018-09-07 evde
2018-09-09 route
2018-09-09 KMOV3 cam
2018-09-10 ttl v4
2018-09-11 KMOv5
2018-09-12 v5rev
2018-09-12 kmoV5rev
2018-09-12 kmoV5befTest
2018-09-13 kmoSrv
2018-09-17 kmoiov6
2018-09-18 7rev
2018-09-19 rev7 out
2018-09-20 v8out
2018-10-01 v9 init
2018-10-01 v9rev
2018-10-25 v1
    lock
2018-10-29 v1.1
2018-12-28 IO BL rev
2019-01-07 1.1 inductance value rev
2019-01-08 out led rev
2019-01-08 al con
2019-01-08 1.1a
2019-01-09 11 ok
2019-01-10 befProduct1.1
2019-01-10 1.1Production
2019-02-15 v12 bl rev
2019-02-15 1.2 edge label
2019-02-25 12 inductor rev
2019-03-13 kapasitör value
2019-03-26 connector rew 3,81
2019-04-29 3d 2v bef test
2019-04-29 v2 cam
2019-04-30 3d some
2019-04-30 3d almost done
2019-04-30 tata
2019-05-03 v2.2
2019-05-03 v2.2 cam
2019-05-05 2.3Cam
2019-05-24 2.4 cam
2019-05-27 end
    2.4 görsel revizyonlar, 2.3 test edildiklten sonra, prototip üretimi yapılabilri durumda
2019-05-27 bmp.scr Deleted
2019-05-29 end of end
2019-05-29 silkscr rev
2019-05-29 cam data
2019-06-11 kabuk
2019-06-21 lm value upd
2019-07-05 25pic
2019-07-07 2.5 silk scr
2019-07-07 2.5pic
2019-09-10 26 cam
2019-10-03 27pic
2019-10-03 27cam
2019-11-04 2.8 min
2019-11-07 min mout 2.9
2019-11-07 29mout
2019-11-26 heat sing
2019-11-26 sht30 check
2019-11-28 2.9 prod
2020-01-09 91 man

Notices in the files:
KMO_IO_M/KMO_IO_MV2_91.brd:
IOTECH © 2020
parts and their libraries:
SparkFun-DiscreteSemi: Licensing: Creative Commons ShareAlike 4.0 International - https://creativecommons.org/licenses/by-sa/4.0
crystal-geyer_V1_0: Copyright: Geyer-Electronic
